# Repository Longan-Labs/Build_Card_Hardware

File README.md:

In the last post, we introduced how to modify and create the firmware of a Card. In this post, we will introduce how to create the hardware of a Card module.
If you want to know which Card modules are currently available, you can click the [link](http://docs.longan-labs.cc/cards-system-summary/) to get the list.

# Required skills

* Familiar with basic electronic circuit
* Familiar with Eagle CAD software

# Download a template

We provide a template of Eagle files to help you to develop quickly. You can click the [link](https://github.com/Longan-Labs/Build_Card_Hardware/archive/master.zip) to download the template.

Open the template and you'll find that the basic part of the schematic has been completed. You only need to add the components you need in the blank part on the left.

# How to design

In the schematic diagram, you can see a device called U1, which is the smallest system module of a single-chip microcomputer. The available interfaces are as follows:

* I2C x 1
* UART x 1
* SPI x 1
* Analog input x 2
* Digital Input/Output x 2

If you use an I2C interface, please connect the I2C of the device to DSDA/DSCL. Similarly, for others interfaces, such as UART/SPI or Analog Input device, do the same things.

In addition, you should pay attention to the power supply. If the device you are using is 3.3V, you need to connect the VCC of U1 to 3V3 of U1, otherwise you can connect it to 5V

# one example

In order to prove that it is not difficult to create a Card module, here we take BME280 as an example to design a BME280 Card.
BME280 is a temperature, humidity and pressure sensor.

As you can see, we put in a BME280 chip, and made some simple connections, and we are done.
You can download Eagle File of BME280 Card for more information.

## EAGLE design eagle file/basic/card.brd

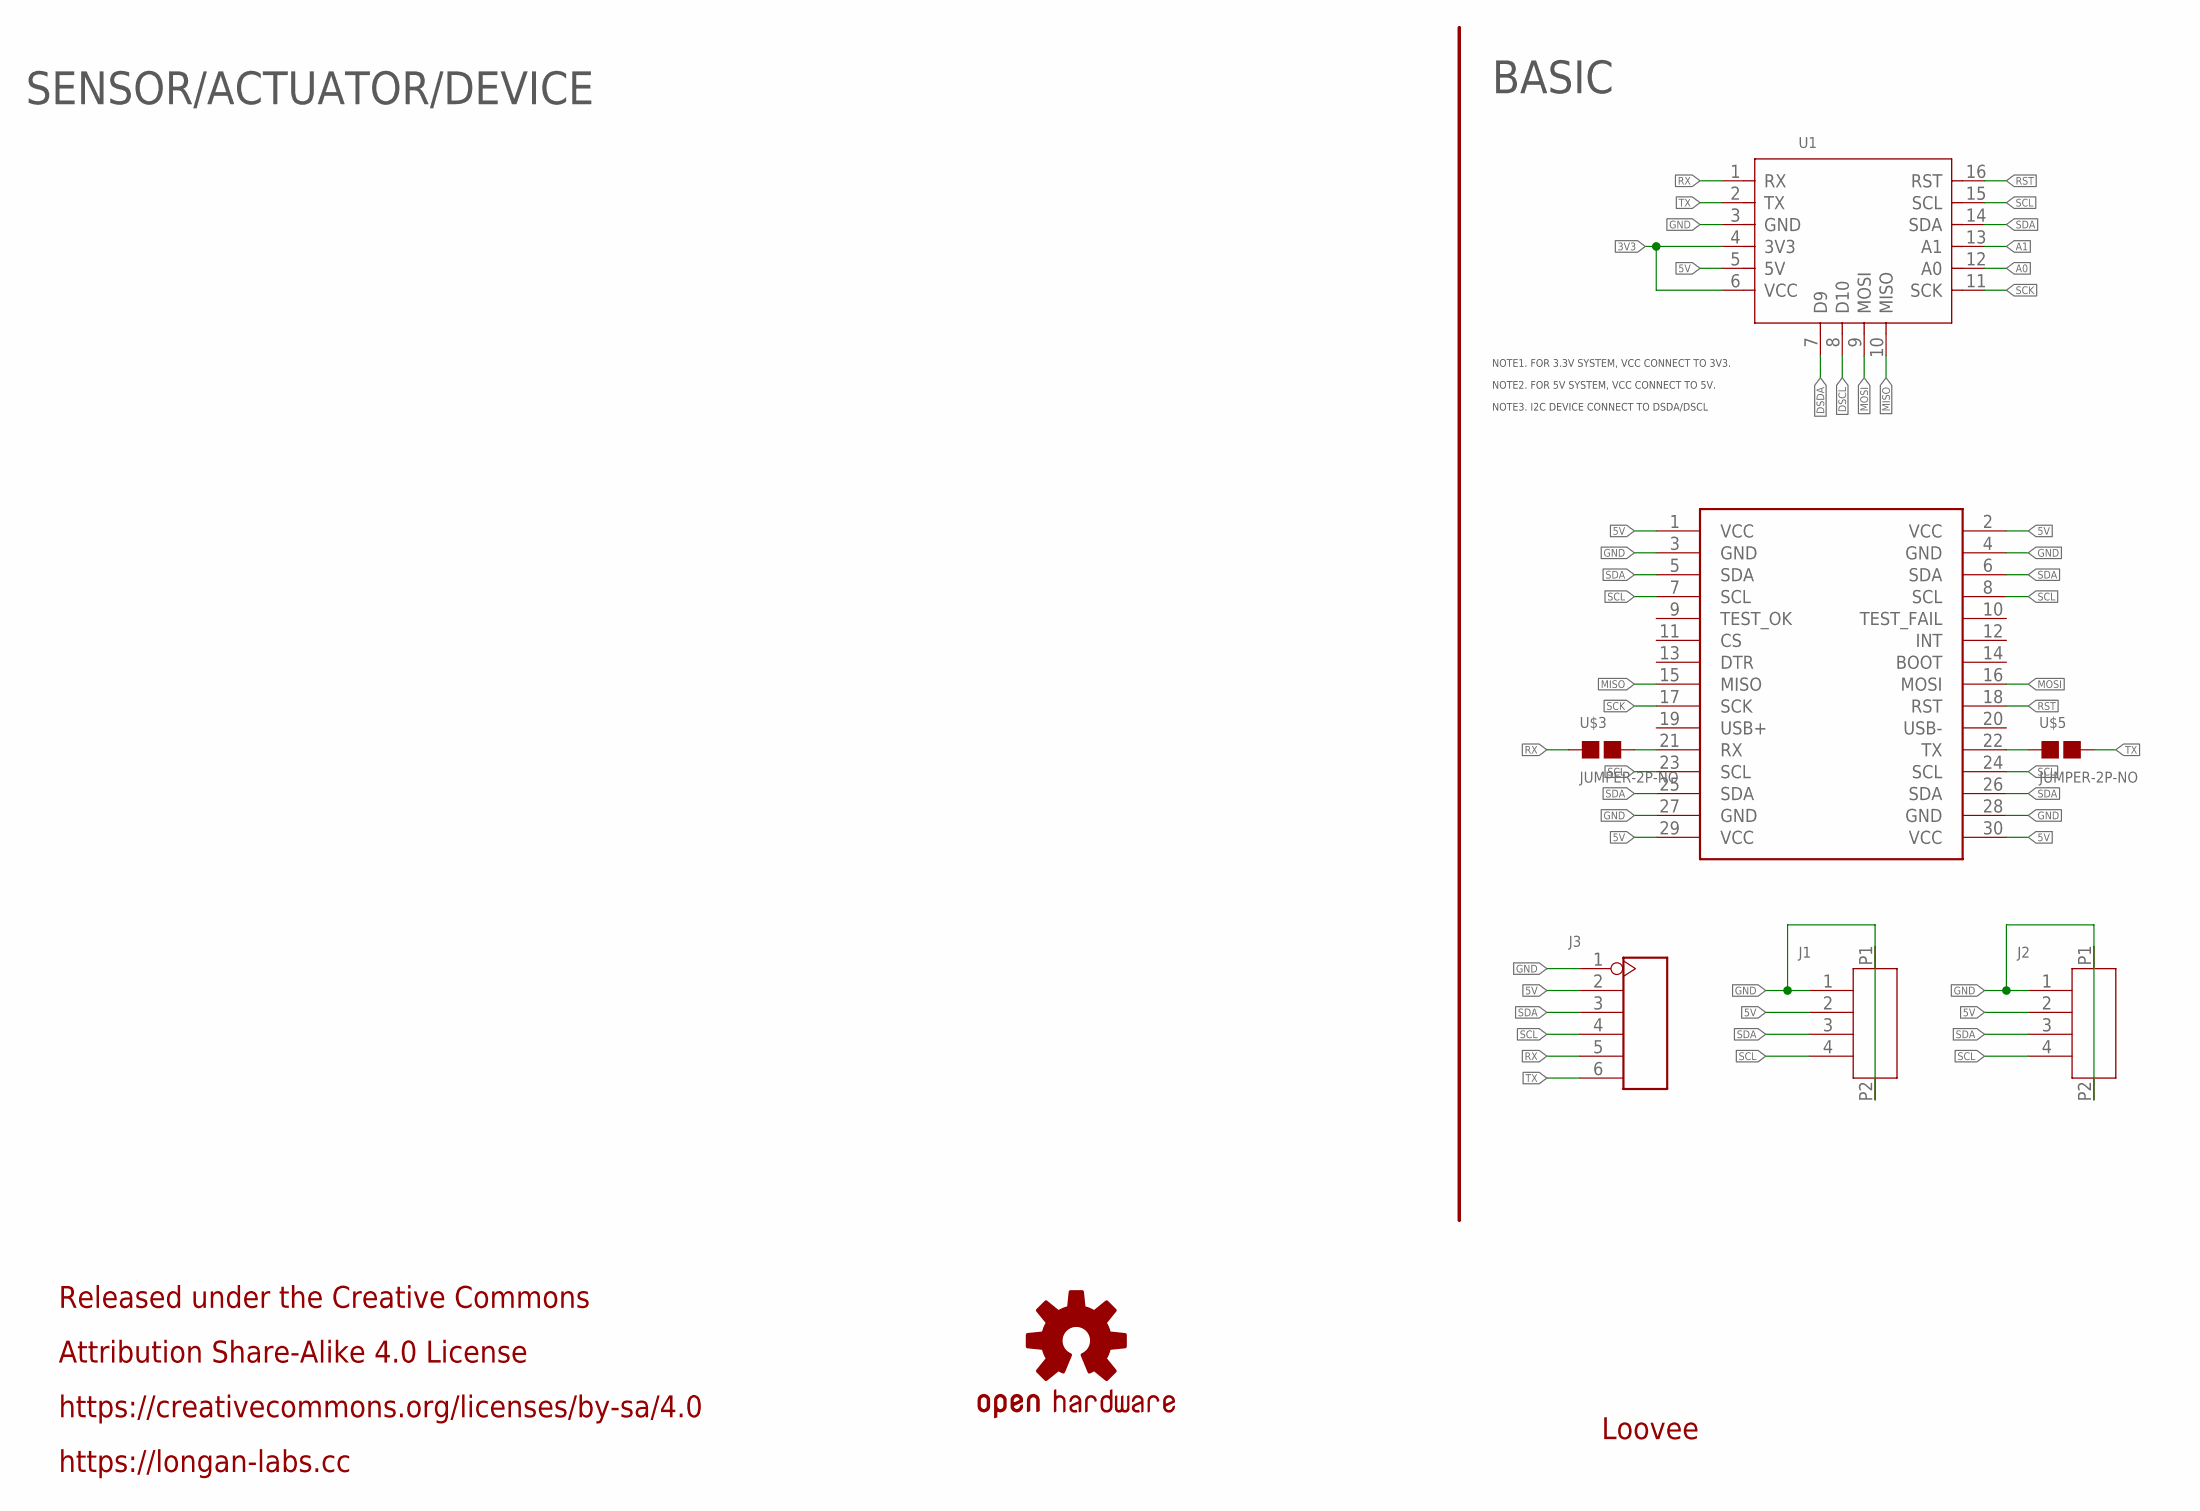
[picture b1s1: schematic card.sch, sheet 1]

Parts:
J1, J2: HEADER-4P-1.0; 4P-1.0-90D
J3: HEADER-6P-55/35MIL; H6-2.54
LOGO2: OSHW-LOGOS; OSHW-LOGO-S
MOUDLE1: MOUDLE-2X15P-2.54'BOARD'; MOUDLE-2X15P-2.54
U1: MOUDLE-CARDS; 16P-2.0-CARDS
U$3, U$5: JUMPER-2P-NO; 2P-SMD-NO

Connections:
3V3: U1.4 (3V3), U1.6 (VCC)
5V: J1.2, J2.2, J3.2, MOUDLE1.1 (VCC), MOUDLE1.2 (VCC), MOUDLE1.29 (VCC), MOUDLE1.30 (VCC), U1.5 (5V)
A0: U1.12 (A0)
A1: U1.13 (A1)
DSCL: U1.8 (D10)
DSDA: U1.7 (D9)
GND: J1.1, J1.P1, J1.P2, J2.1, J2.P1, J2.P2, J3.1, MOUDLE1.3 (GND), MOUDLE1.4 (GND), MOUDLE1.27 (GND), MOUDLE1.28 (GND), U1.3 (GND)
MISO: MOUDLE1.15 (MISO), U1.10 (MISO)
MOSI: MOUDLE1.16 (MOSI), U1.9 (MOSI)
unnamed: MOUDLE1.21 (RX), U$3.2
unnamed: MOUDLE1.22 (TX), U$5.1
RST: MOUDLE1.18 (RST), U1.16 (RST)
RX: J3.5, U1.1 (RX), U$3.1
SCK: MOUDLE1.17 (SCK), U1.11 (SCK)
SCL: J1.4, J2.4, J3.4, MOUDLE1.7 (SCL), MOUDLE1.8 (SCL), MOUDLE1.23 (SCL), MOUDLE1.24 (SCL), U1.15 (SCL)
SDA: J1.3, J2.3, J3.3, MOUDLE1.5 (SDA), MOUDLE1.6 (SDA), MOUDLE1.25 (SDA), MOUDLE1.26 (SDA), U1.14 (SDA)
TX: J3.6, U1.2 (TX), U$5.2

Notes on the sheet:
BASIC
Loovee
NOTE1. FOR 3.3V SYSTEM, VCC CONNECT TO 3V3.
NOTE2. FOR 5V SYSTEM, VCC CONNECT TO 5V.
NOTE3. I2C DEVICE CONNECT TO DSDA/DSCL
SENSOR/ACTUATOR/DEVICE
Released under the Creative Commons
Attribution Share-Alike 4.0 License
https://creativecommons.org/licenses/by-sa/4.0
https://longan-labs.cc

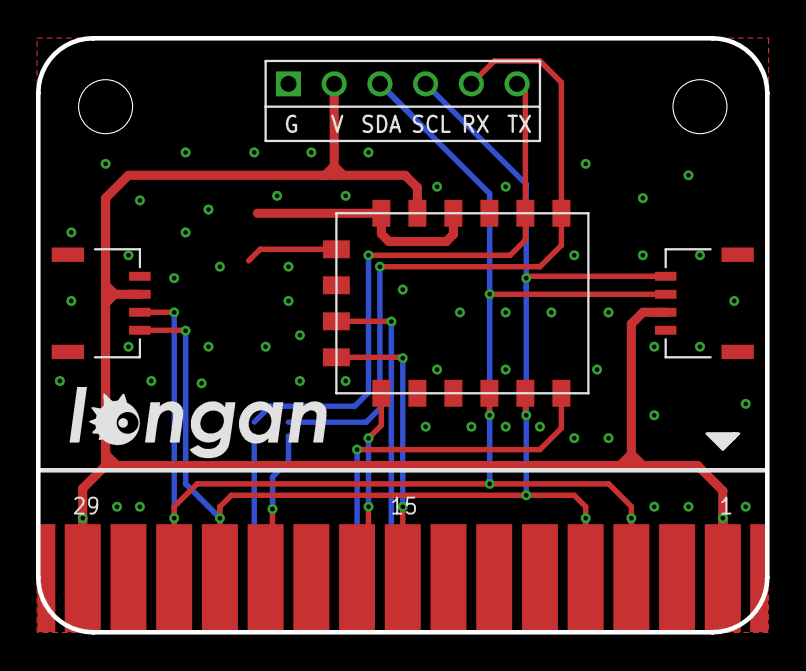
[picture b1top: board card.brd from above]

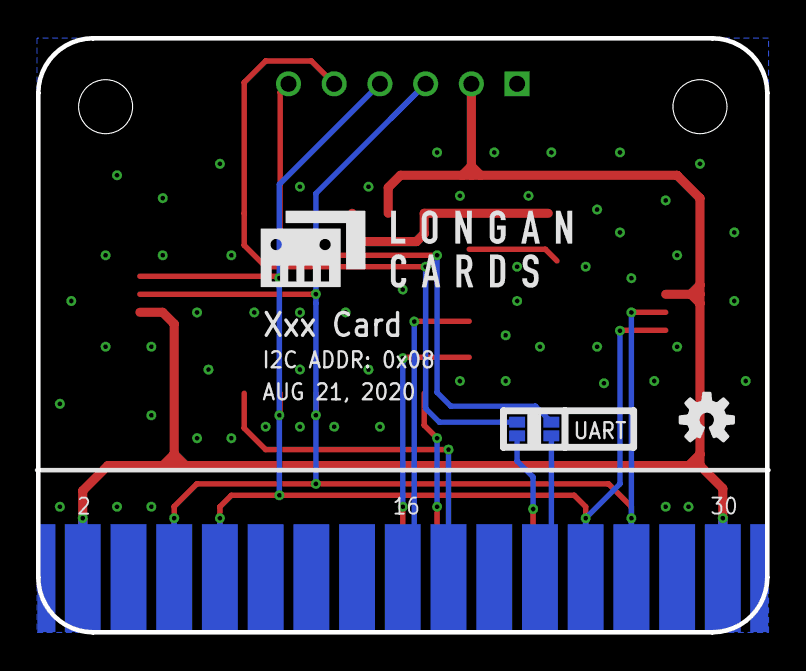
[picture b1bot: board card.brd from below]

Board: 2 copper layers, 40.5 x 33.0 mm, 10 parts (4 on the bottom side), 13 nets.

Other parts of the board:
U$1: LONGAN-CARDS-MIDDLE
U$2: LONGAN-SILK-SMALLER

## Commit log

2020-09-24 add images

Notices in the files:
parts and their libraries:
SparkFun-Aesthetics: Licensing: CC v3.0 Share-Alike You are welcome to use this library for commercial purposes.
